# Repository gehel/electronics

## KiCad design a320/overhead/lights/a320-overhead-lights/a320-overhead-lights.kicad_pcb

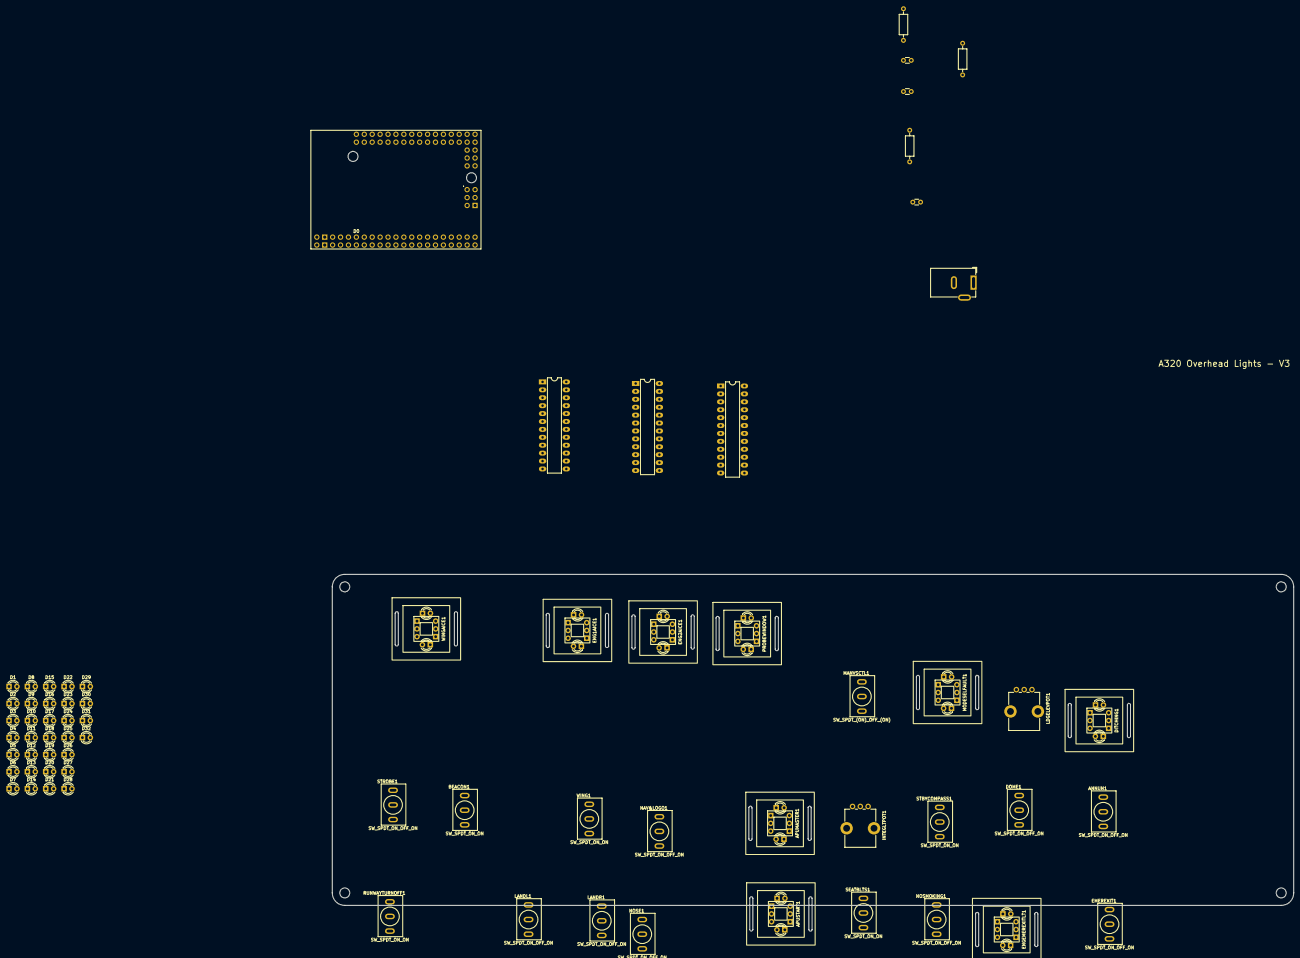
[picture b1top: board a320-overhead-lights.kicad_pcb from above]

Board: 2 copper layers, 308.6 x 119.5 mm, 73 parts (0 on the bottom side), 98 nets, no tracks yet.

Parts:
A1: Clone_Mega2560_Pro_Socket
ANNUN1: SW_SPDT_ON_OFF_ON; ToggleSwitch_MTS-102_SPDT
APUMASTER1: Korry Switch
APUSTART1: Korry Switch
BEACON1: SW_SPDT_ON_ON; ToggleSwitch_MTS-102_SPDT
C1, C2, C3: 100nF; C_Disc_D3.0mm_W1.6mm_P2.50mm
D1, D2, D3, D4, D5, D6, D7, D8, D9, D10, D11, D12, D13, D14, D15, D16, D17, D18, D19, D20, D21, D22, D23, D24, D25, D26, D27, D28, D29, D30, D31, D32: LED; LED_D3.0mm
DITCHING1: Korry Switch
DOME1: SW_SPDT_ON_OFF_ON; ToggleSwitch_MTS-102_SPDT
EMEREXIT1: SW_SPDT_ON_OFF_ON; ToggleSwitch_MTS-102_SPDT
ENG1AICE1, ENG2AICE1: Korry Switch
ENGEMEREXITLT1: Korry Switch
H1, H2, H3, H4: MountingHole; MountingHole_3.2mm_M3
INTEGLTPOT1: 10K; Potentiometer_Bourns_PTV09A-1_Single_Vertical
J9: Barrel_Jack; BarrelJack_GCT_DCJ200-10-A_Horizontal
LANDL1: SW_SPDT_ON_OFF_ON; ToggleSwitch_MTS-102_SPDT
LANDR1: SW_SPDT_ON_OFF_ON; ToggleSwitch_MTS-102_SPDT
LDGELEVPOT1: 10K; Potentiometer_Bourns_PTV09A-1_Single_Vertical
MANVSCTL1: SW_SPDT_(ON)_OFF_(ON); ToggleSwitch_MTS-102_SPDT
MODESELFAULT1: Korry Switch
NAV&LOGO1: SW_SPDT_ON_OFF_ON; ToggleSwitch_MTS-102_SPDT
NOSE1: SW_SPDT_ON_OFF_ON; ToggleSwitch_MTS-102_SPDT
NOSMOKING1: SW_SPDT_ON_OFF_ON; ToggleSwitch_MTS-102_SPDT
PROBEWINDOW1: Korry Switch
R1, R2, R3: 1K; R_Axial_DIN0207_L6.3mm_D2.5mm_P10.16mm_Horizontal
RUNWAYTURNOFF1: SW_SPDT_ON_ON; ToggleSwitch_MTS-102_SPDT
SEATBLTS1: SW_SPDT_ON_ON; ToggleSwitch_MTS-102_SPDT
STBYCOMPASS1: SW_SPDT_ON_ON; ToggleSwitch_MTS-102_SPDT
STROBE1: SW_SPDT_ON_OFF_ON; ToggleSwitch_MTS-102_SPDT
U1, U2, U3: LED1642GWPTR; DIP-24_W7.62mm_LongPads
WING1: SW_SPDT_ON_ON; ToggleSwitch_MTS-102_SPDT
WINGAICE1: Korry Switch

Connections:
+5V: A1.5V1 (5V), A1.5V2 (SPI_5V), A1.5V3 (5V), APUMASTER1.2 (A), APUMASTER1.10 (A), APUSTART1.2 (A), APUSTART1.10 (A), C1.1, C2.1, C3.1, DITCHING1.2 (A), DITCHING1.10 (A), ENG1AICE1.2 (A), ENG1AICE1.10 (A), ENG2AICE1.2 (A), ENG2AICE1.10 (A), ENGEMEREXITLT1.2 (A), ENGEMEREXITLT1.10 (A), INTEGLTPOT1.3, LDGELEVPOT1.3, MODESELFAULT1.2 (A), MODESELFAULT1.10 (A), PROBEWINDOW1.2 (A), PROBEWINDOW1.10 (A), U1.24 (VDD), U2.24 (VDD), U3.24 (VDD), WINGAICE1.2 (A), WINGAICE1.10 (A)
+12V: D1.2 (A), D2.2 (A), D3.2 (A), D4.2 (A), D5.2 (A), D6.2 (A), D7.2 (A), D8.2 (A), J9.1
ANNUNCIATOR_BRT: A1.D3 (D3_INT1), U1.21 (PWCLK), U3.21 (PWCLK)
BACKLIGHT_0: D25.1 (K), U2.5 (OUT0)
BACKLIGHT_1: D26.1 (K), U2.6 (OUT1)
BACKLIGHT_2: D27.1 (K), U2.7 (OUT2)
BACKLIGHT_3: D28.1 (K), U2.8 (OUT3)
BACKLIGHT_4: D29.1 (K), U2.9 (OUT4)
BACKLIGHT_5: D30.1 (K), U2.10 (OUT5)
BACKLIGHT_6: D31.1 (K), U2.11 (OUT6)
BACKLIGHT_7: D32.1 (K), U2.12 (OUT7)
BACKLIGHT_BRT: A1.D2 (D2_INT0), U2.21 (PWCLK)
GND: A1.GND1 (GND), A1.GND2 (GND), A1.GND4 (SPI_GND), ANNUN1.2 (B), APUMASTER1.3 (COM1), APUSTART1.3 (COM1), BEACON1.2 (B), C1.2, C2.2, C3.2, DITCHING1.3 (COM1), DOME1.2 (B), EMEREXIT1.2 (B), ENG1AICE1.3 (COM1), ENG2AICE1.3 (COM1), ENGEMEREXITLT1.3 (COM1), INTEGLTPOT1.1, INTEGLTPOT1.MP (MountPin), J9.2, LANDL1.2 (B), LANDR1.2 (B), LDGELEVPOT1.1, LDGELEVPOT1.MP (MountPin), MANVSCTL1.2 (B), MODESELFAULT1.3 (COM1), NAV&LOGO1.2 (B), NOSE1.2 (B), NOSMOKING1.2 (B), PROBEWINDOW1.3 (COM1), R1.1, R2.1, R3.1, RUNWAYTURNOFF1.2 (B), SEATBLTS1.2 (B), STBYCOMPASS1.2 (B), STROBE1.2 (B), U1.1 (GND), U2.1 (GND), U3.1 (GND), WING1.2 (B), WINGAICE1.3 (COM1)
LEDDRV_CLK: A1.A1, U1.3 (CLK), U2.3 (CLK), U3.3 (CLK)
LEDDRV_DATA: A1.A2, U1.2 (SDI)
LEDDRV_DATA_2: U1.22 (SDO), U3.2 (SDI)
LEDDRV_DATA_3: U2.2 (SDI), U3.22 (SDO)
LEDDRV_LATCH: A1.A0, U1.4 (LE), U2.4 (LE), U3.4 (LE)
unnamed: D1.1 (K), D9.2 (A)
unnamed: D2.1 (K), D10.2 (A)
unnamed: D10.1 (K), D18.2 (A)
unnamed: D3.1 (K), D11.2 (A)
unnamed: D11.1 (K), D19.2 (A)
unnamed: D4.1 (K), D12.2 (A)
unnamed: D12.1 (K), D20.2 (A)
unnamed: D5.1 (K), D13.2 (A)
unnamed: D13.1 (K), D21.2 (A)
unnamed: D6.1 (K), D14.2 (A)
unnamed: D14.1 (K), D22.2 (A)
unnamed: D7.1 (K), D15.2 (A)
unnamed: D15.1 (K), D23.2 (A)
unnamed: D8.1 (K), D16.2 (A)
unnamed: D16.1 (K), D24.2 (A)
unnamed: D9.1 (K), D17.2 (A)
unnamed: D17.1 (K), D25.2 (A)
unnamed: D18.1 (K), D26.2 (A)
unnamed: D19.1 (K), D27.2 (A)
unnamed: D20.1 (K), D28.2 (A)
unnamed: D21.1 (K), D29.2 (A)
unnamed: D22.1 (K), D30.2 (A)
unnamed: D23.1 (K), D31.2 (A)
unnamed: D24.1 (K), D32.2 (A)
unnamed: R1.2, U1.23 (R-EXT)
unnamed: R2.2, U2.23 (R-EXT)
unnamed: R3.2, U3.23 (R-EXT)
annunbrt: A1.D33, ANNUN1.3 (C)
annunoff: A1.D34, ANNUN1.1 (A)
apumaster: A1.D5, APUMASTER1.4 (NO1)
apumasterfault: APUMASTER1.1 (K), U1.17 (OUT12)
apumasteron: APUMASTER1.9 (K), U1.18 (OUT13)
apustart: A1.D4, APUSTART1.4 (NO1)
apustartfault: APUSTART1.1 (K), U1.19 (OUT14)
apustarton: APUSTART1.9 (K), U1.20 (OUT15)
beaconon: A1.D16 (D16/TX2), BEACON1.3 (C)
ditching: A1.D41, DITCHING1.4 (NO1)
ditchingfault: DITCHING1.1 (K), MODESELFAULT1.1 (K), U3.5 (OUT0)
ditchingon: DITCHING1.9 (K), U3.6 (OUT1)
domebrt: A1.A15, DOME1.3 (C)
domedim: A1.D32, DOME1.1 (A)
emerexitlt: A1.A11, ENGEMEREXITLT1.4 (NO1)
emerexitltfault: ENGEMEREXITLT1.1 (K), U3.7 (OUT2)
emerexitltoff: ENGEMEREXITLT1.9 (K), U3.8 (OUT3)
emerexitoff: A1.A13, EMEREXIT1.1 (A)
emerexiton: A1.A12, EMEREXIT1.3 (C)
eng1aice: A1.D35, ENG1AICE1.4 (NO1)
eng1aicefault: ENG1AICE1.1 (K), U1.9 (OUT4)
eng1aiceon: ENG1AICE1.9 (K), U1.10 (OUT5)
eng2aice: A1.D36, ENG2AICE1.4 (NO1)
eng2aicefault: ENG2AICE1.1 (K), U1.11 (OUT6)
eng2aiceon: ENG2AICE1.9 (K), U1.12 (OUT7)
integltpot: A1.A4, INTEGLTPOT1.2
landlon: A1.D14 (D14/TX3), LANDL1.3 (C)
landlretract: A1.D15 (D15/RX3), LANDL1.1 (A)
landron: A1.D17 (D17/RX2), LANDR1.3 (C)
landrretract: A1.D12, LANDR1.1 (A)
ldgelevpot: A1.A3, LDGELEVPOT1.2
manvsctloff: A1.D39, MANVSCTL1.1 (A)
manvsctlon: A1.D38, MANVSCTL1.3 (C)
modesel: A1.D40, MODESELFAULT1.4 (NO1)
modeselon: MODESELFAULT1.9 (K), U1.16 (OUT11)
nav&logooff: A1.D7, NAV&LOGO1.1 (A)
nav&logoon: A1.D8, NAV&LOGO1.3 (C)
noseoff: A1.D9, NOSE1.1 (A)
noseon: A1.D10, NOSE1.3 (C)
nosmokingoff: A1.A10, NOSMOKING1.1 (A)
nosmokingon: A1.A9, NOSMOKING1.3 (C)
probewindow: A1.D37, PROBEWINDOW1.4 (NO1)
probewindowfault: PROBEWINDOW1.1 (K), U1.13 (OUT8)
probewindowoff: PROBEWINDOW1.9 (K), U1.14 (OUT9)
runwayturnoffon: A1.D20 (D20/SDA), RUNWAYTURNOFF1.3 (C)
seatbeltson: A1.A8, SEATBLTS1.3 (C)
stbycompasson: A1.A14, STBYCOMPASS1.3 (C)
strobeoff: A1.D31, STROBE1.3 (C)
strobeon: A1.D21 (D21/SCL), STROBE1.1 (A)
wingaice: A1.D18 (D18/TX1), WINGAICE1.4 (NO1)
wingaicefault: U1.5 (OUT0), WINGAICE1.1 (K)
wingaiceon: U1.6 (OUT1), WINGAICE1.9 (K)
wingon: A1.D11, WING1.3 (C)

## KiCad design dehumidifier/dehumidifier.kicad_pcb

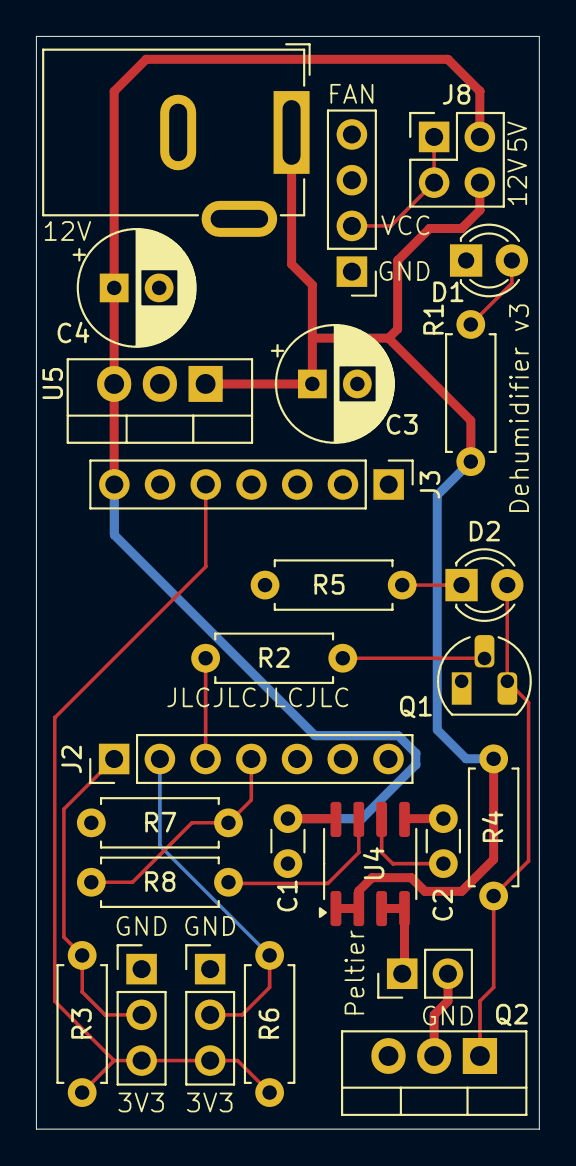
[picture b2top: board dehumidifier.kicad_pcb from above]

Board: 2 copper layers, 27.9 x 60.7 mm, 26 parts (0 on the bottom side), 17 nets.

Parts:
C1, C2: 100nF; C_Disc_D3.0mm_W1.6mm_P2.50mm
C3, C4: C_Polarized; CP_Radial_D6.3mm_P2.50mm
D1, D2: LED; LED_D3.0mm
J1: Barrel_Jack_Switch; BarrelJack_GCT_DCJ200-10-A_Horizontal
J2, J3: Conn_01x07; PinHeader_1x07_P2.54mm_Vertical
J4, J7: Conn_01x03_Pin; PinHeader_1x03_P2.54mm_Vertical
J5: Conn_01x02_Pin; PinHeader_1x02_P2.54mm_Vertical
J6: Conn_01x04_Pin; PinHeader_1x04_P2.54mm_Vertical
J8: Conn_02x02_Odd_Even; PinHeader_2x02_P2.54mm_Vertical
Q1: 2N3904; TO-92_HandSolder
Q2: Q_NMOS_GDS; TO-220-3_Vertical
R1: 1K5; R_Axial_DIN0207_L6.3mm_D2.5mm_P7.62mm_Horizontal
R2, R4, R7: 10K; R_Axial_DIN0207_L6.3mm_D2.5mm_P7.62mm_Horizontal
R3, R8: 4K7; R_Axial_DIN0207_L6.3mm_D2.5mm_P7.62mm_Horizontal
R5: 470R; R_Axial_DIN0207_L6.3mm_D2.5mm_P7.62mm_Horizontal
R6: 2K7; R_Axial_DIN0207_L6.3mm_D2.5mm_P7.62mm_Horizontal
U4: ACS712xLCTR-05B; SOIC-8_3.9x4.9mm_P1.27mm
U5: LM78M05_TO220; TO-220-3_Vertical

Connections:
+3V3: J3.5, J4.3, J7.3, R3.1, R6.1
+5V: C1.1, C4.1, J3.7, J8.2, U4.8 (VCC), U5.3 (VO)
+12V: C3.1, J1.1, J8.4, R1.2, R4.2, U4.1 (IP+), U4.2 (IP+), U5.1 (VI)
CURRENT: J2.4, R7.1, R8.2
DHT11_DATA: J2.1, J4.2, R3.2
DS18B20_DATA: J2.2, J7.2, R6.2
GND: C1.2, C2.2, C3.2, C4.2, D1.1 (K), J1.2, J3.6, J4.1, J6.1, J7.1, Q1.1 (E), Q2.3 (S), R5.1, R7.2, U4.5 (GND), U5.2 (GND)
unnamed: D1.2 (A), R1.1
unnamed: D2.2 (A), Q1.3 (C), Q2.1 (G), R4.1
unnamed: D2.1 (K), R5.2
unnamed: J5.1, U4.3 (IP-), U4.4 (IP-)
unnamed: J5.2, Q2.2 (D)
unnamed: Q1.2 (B), R2.2
unnamed: C2.1, U4.6 (FILTER)
unnamed: R8.1, U4.7 (VIOUT)
PELTIER_CTRL: J2.3, R2.1
V_FAN: J6.2, J8.1, J8.3

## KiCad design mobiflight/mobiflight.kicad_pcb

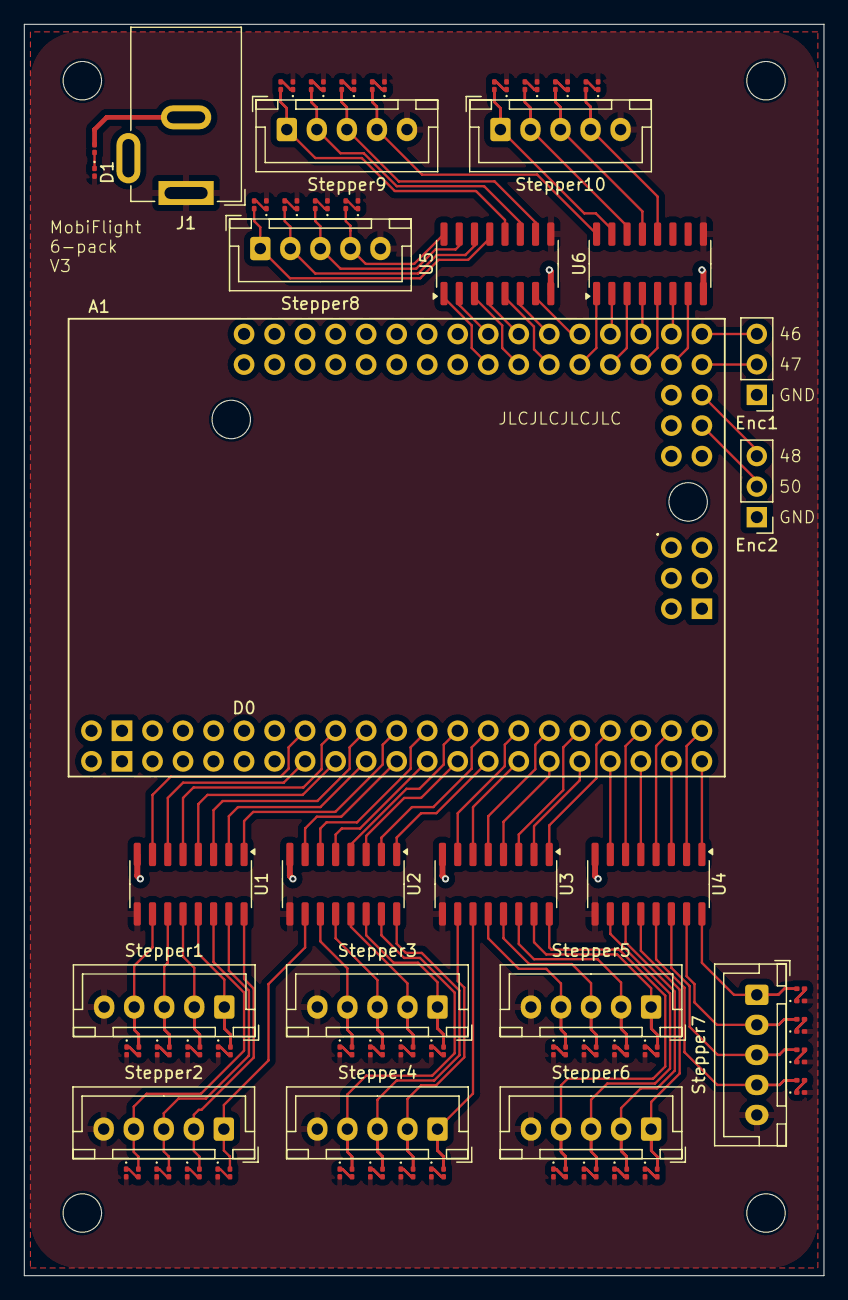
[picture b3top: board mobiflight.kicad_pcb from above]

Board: 2 copper layers, 66.5 x 104.1 mm, 106 parts (0 on the bottom side), 129 nets.

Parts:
A1: Clone_Mega2560_Pro_Socket
D1, D2, D3, D4, D5, D6, D7, D8, D9, D10, D11, D12, D13, D14, D15, D16, D17, D18, D19, D20, D21, D22, D23, D24, D25, D26, D27, D28, D29, D30, D31, D32, D33, D34, D35, D36, D37, D38, D39, D40, D41: LED; LED_0201_0603Metric
Enc1, Enc2: Conn_01x03_Pin; PinHeader_1x03_P2.54mm_Vertical
H1, H2, H3, H4: MountingHole; MountingHole_3.2mm_M3
J1: Barrel_Jack_Switch; BarrelJack_GCT_DCJ200-10-A_Horizontal
R1, R2, R3, R4, R5, R6, R7, R8, R9, R10, R11, R12, R13, R14, R15, R16, R17, R18, R19, R20, R21, R22, R23, R24, R25, R26, R27, R28, R29, R30, R31, R32, R33, R34, R35, R36, R37, R38, R39, R40, R41: 470R; R_0201_0603Metric
Stepper1, Stepper2, Stepper3, Stepper4, Stepper5, Stepper6, Stepper7, Stepper8, Stepper9, Stepper10: Conn_01x05_Pin; JST_XH_B5B-XH-A_1x05_P2.50mm_Vertical
U1, U2, U3, U4, U5, U6: ULN2003; SOIC-16_3.9x9.9mm_P1.27mm

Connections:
D4: A1.D4, U1.7 (I7)
D5: A1.D5, U1.6 (I6)
D6: A1.D6, U1.5 (I5)
D7: A1.D7, U1.4 (I4)
D8: A1.D8, U1.3 (I3)
D9: A1.D9, U1.2 (I2)
D10: A1.D10, U1.1 (I1)
D11: A1.D11, U2.7 (I7)
D12: A1.D12, U2.6 (I6)
D13: A1.D13, U2.5 (I5)
D14: A1.D14 (D14/TX3), U2.4 (I4)
D15: A1.D15 (D15/RX3), U2.3 (I3)
D16: A1.D16 (D16/TX2), U2.2 (I2)
D17: A1.D17 (D17/RX2), U2.1 (I1)
D18: A1.D18 (D18/TX1), U3.7 (I7)
D19: A1.D19 (D19/RX1), U3.6 (I6)
D20: A1.D20 (D20/SDA), U3.5 (I5)
D21: A1.D21 (D21/SCL), U3.4 (I4)
D22: A1.D22, U3.3 (I3)
D23: A1.D23, U3.2 (I2)
D24: A1.D24, U3.1 (I1)
D25: A1.D25, U4.7 (I7)
D26: A1.D26, U4.6 (I6)
D27: A1.D27, U4.5 (I5)
D28: A1.D28, U4.4 (I4)
D29: A1.D29, U4.3 (I3)
D30: A1.D30, U4.2 (I2)
D31: A1.D31, U4.1 (I1)
D32: A1.D32, U5.2 (I2)
D33: A1.D33, U5.1 (I1)
D34: A1.D34, U5.4 (I4)
D35: A1.D35, U5.3 (I3)
D36: A1.D36, U5.6 (I6)
D37: A1.D37, U5.5 (I5)
D38: A1.D38, U5.7 (I7)
D39: A1.D39, U6.1 (I1)
D40: A1.D40, U6.2 (I2)
D41: A1.D41, U6.3 (I3)
D42: A1.D42, U6.4 (I4)
D43: A1.D43, U6.5 (I5)
D44: A1.D44, U6.6 (I6)
D45: A1.D45, U6.7 (I7)
GND: A1.GND1 (GND), A1.GND2 (GND), Enc1.1, Enc2.1, J1.2, R1.2, U1.8 (GND), U2.8 (GND), U3.8 (GND), U4.8 (GND), U5.8 (GND), U6.8 (GND)
unnamed: A1.D50 (D50_MISO), Enc2.2
unnamed: D1.1 (K), R1.1
unnamed: D2.1 (K), R2.1
unnamed: D3.1 (K), R3.1
unnamed: D4.1 (K), R4.1
unnamed: D5.1 (K), R5.1
unnamed: D6.1 (K), R6.1
unnamed: D7.1 (K), R7.1
unnamed: D8.1 (K), R8.1
unnamed: D9.1 (K), R9.1
unnamed: D10.1 (K), R10.1
unnamed: D11.1 (K), R11.1
unnamed: D12.1 (K), R12.1
unnamed: D13.1 (K), R13.1
unnamed: D14.1 (K), R14.1
unnamed: D15.1 (K), R15.1
unnamed: D16.1 (K), R16.1
unnamed: D17.1 (K), R17.1
unnamed: D18.1 (K), R18.1
unnamed: D19.1 (K), R19.1
unnamed: D20.1 (K), R20.1
unnamed: D21.1 (K), R21.1
unnamed: D22.1 (K), R22.1
unnamed: D23.1 (K), R23.1
unnamed: D24.1 (K), R24.1
unnamed: D25.1 (K), R25.1
unnamed: D26.1 (K), R26.1
unnamed: D27.1 (K), R27.1
unnamed: D28.1 (K), R28.1
unnamed: D29.1 (K), R29.1
unnamed: D30.1 (K), R30.1
unnamed: D31.1 (K), R31.1
unnamed: D32.1 (K), R32.1
unnamed: D33.1 (K), R33.1
unnamed: D34.1 (K), R34.1
unnamed: D35.1 (K), R35.1
unnamed: D36.1 (K), R36.1
unnamed: D37.1 (K), R37.1
unnamed: D38.1 (K), R38.1
unnamed: D39.1 (K), R39.1
unnamed: D40.1 (K), R40.1
unnamed: D41.1 (K), R41.1
unnamed: A1.D47, Enc1.2
unnamed: A1.D46, Enc1.3
unnamed: A1.D48, Enc2.3
S1_1: R2.2, Stepper1.1, U1.13 (O4)
S1_2: R3.2, Stepper1.2, U1.12 (O5)
S1_3: R4.2, Stepper1.3, U1.11 (O6)
S1_4: R5.2, Stepper1.4, U1.10 (O7)
S2_1: R38.2, Stepper2.1, U2.10 (O7)
S2_2: R39.2, Stepper2.2, U1.16 (O1)
S2_3: R40.2, Stepper2.3, U1.15 (O2)
S2_4: R41.2, Stepper2.4, U1.14 (O3)
S3_1: R6.2, Stepper3.1, U2.14 (O3)
S3_2: R7.2, Stepper3.2, U2.13 (O4)
S3_3: R8.2, Stepper3.3, U2.12 (O5)
S3_4: R9.2, Stepper3.4, U2.11 (O6)
S4_1: R10.2, Stepper4.1, U3.11 (O6)
S4_2: R11.2, Stepper4.2, U3.10 (O7)
S4_3: R12.2, Stepper4.3, U2.16 (O1)
S4_4: R13.2, Stepper4.4, U2.15 (O2)
S5_1: R14.2, Stepper5.1, U3.15 (O2)
S5_2: R15.2, Stepper5.2, U3.14 (O3)
S5_3: R16.2, Stepper5.3, U3.13 (O4)
S5_4: R17.2, Stepper5.4, U3.12 (O5)
S6_1: R18.2, Stepper6.1, U4.12 (O5)
S6_2: R19.2, Stepper6.2, U4.11 (O6)
S6_3: R20.2, Stepper6.3, U4.10 (O7)
S6_4: R21.2, Stepper6.4, U3.16 (O1)
S7_1: R22.2, Stepper7.1, U4.16 (O1)
S7_2: R23.2, Stepper7.2, U4.15 (O2)
S7_3: R24.2, Stepper7.3, U4.14 (O3)
S7_4: R25.2, Stepper7.4, U4.13 (O4)
S8_1: R26.2, Stepper8.1, U5.13 (O4)
S8_2: R27.2, Stepper8.2, U5.14 (O3)
S8_3: R28.2, Stepper8.3, U5.15 (O2)
S8_4: R29.2, Stepper8.4, U5.16 (O1)
S9_1: R30.2, Stepper9.1, U5.12 (O5)
S9_2: R31.2, Stepper9.2, U5.11 (O6)
S9_3: R32.2, Stepper9.3, U5.10 (O7)
S9_4: R33.2, Stepper9.4, U6.16 (O1)
S10_1: R34.2, Stepper10.1, U6.15 (O2)
S10_2: R35.2, Stepper10.2, U6.14 (O3)
S10_3: R36.2, Stepper10.3, U6.13 (O4)
S10_4: R37.2, Stepper10.4, U6.12 (O5)
VCC: D1.2 (A), D2.2 (A), D3.2 (A), D4.2 (A), D5.2 (A), D6.2 (A), D7.2 (A), D8.2 (A), D9.2 (A), D10.2 (A), D11.2 (A), D12.2 (A), D13.2 (A), D14.2 (A), D15.2 (A), D16.2 (A), D17.2 (A), D18.2 (A), D19.2 (A), D20.2 (A), D21.2 (A), D22.2 (A), D23.2 (A), D24.2 (A), D25.2 (A), D26.2 (A), D27.2 (A), D28.2 (A), D29.2 (A), D30.2 (A), D31.2 (A), D32.2 (A), D33.2 (A), D34.2 (A), D35.2 (A), D36.2 (A), D37.2 (A), D38.2 (A), D39.2 (A), D40.2 (A), D41.2 (A), J1.1, Stepper1.5, Stepper2.5, Stepper3.5, Stepper4.5, Stepper5.5, Stepper6.5, Stepper7.5, Stepper8.5, Stepper9.5, Stepper10.5, U1.9 (COM), U2.9 (COM), U3.9 (COM), U4.9 (COM), U5.9 (COM), U6.9 (COM)

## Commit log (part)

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2024-06-24 misc
2024-07-16 fix power connector
2024-07-16 add LEDs, move to SMD
2024-07-17 replace components
2024-07-19 wiring for smd mobiflight
2024-07-26 adding current sensing
2024-07-26 12V for peltier
2025-01-10 a320 overhead lights
2025-01-10 dehumidifier
2025-02-14 a320 overhead lights - added labels to pcb
2025-02-14 a320 overhead lights - fixed wrong cascading of led drivers
2025-02-14 a320 overhead lights - moved led drivers around and re-routed
2025-02-19 Ordered a320 overhead panel
2025-02-21 a320 - korry switch
